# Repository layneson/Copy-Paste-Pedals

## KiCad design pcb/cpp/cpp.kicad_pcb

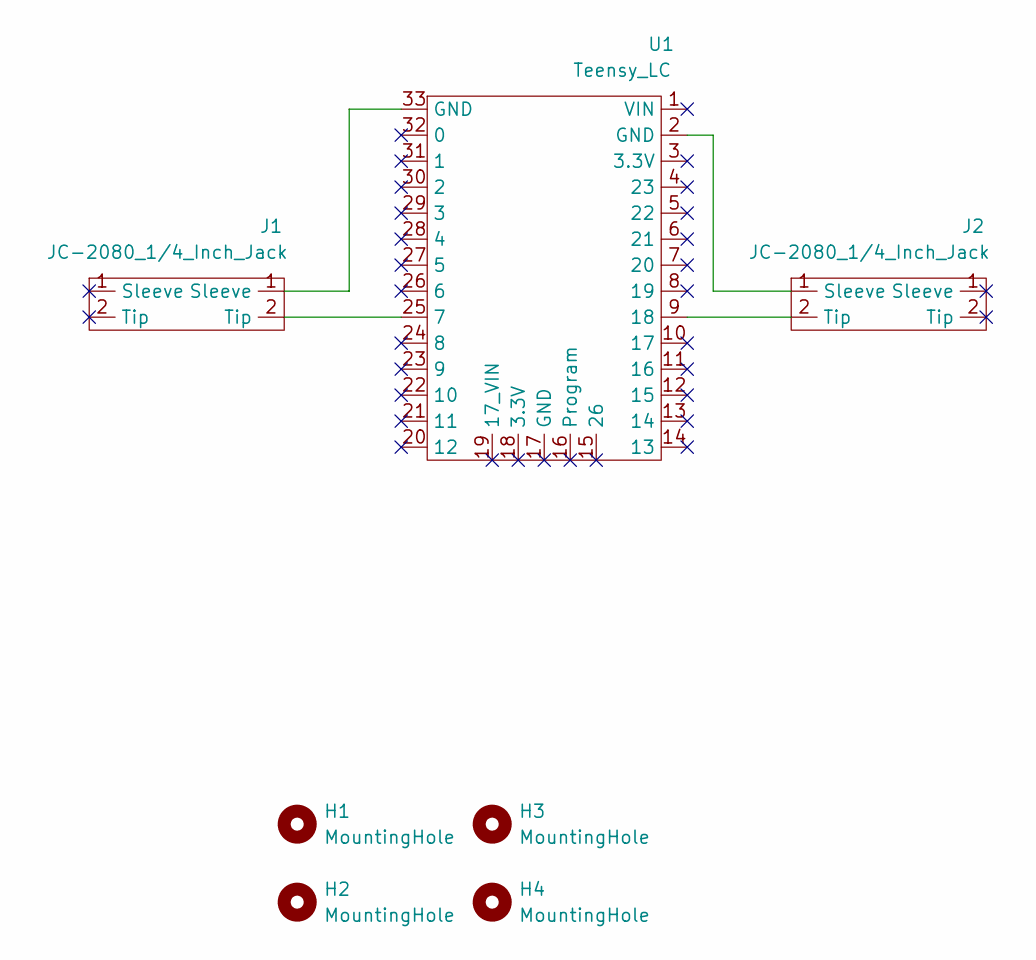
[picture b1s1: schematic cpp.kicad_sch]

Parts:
H1, H2, H3, H4: MountingHole; MountingHole_2.2mm_M2
J1, J2: JC-2080_1/4_Inch_Jack; JC-2080_14_Inch_Jack
U1: Teensy_LC; Teensy LC

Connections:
unnamed: J1.1 (Sleeve), U1.33 (GND)
unnamed: J1.2 (Tip), U1.25 (7)
unnamed: J2.1 (Sleeve), U1.2 (GND)
unnamed: J2.2 (Tip), U1.9 (18)

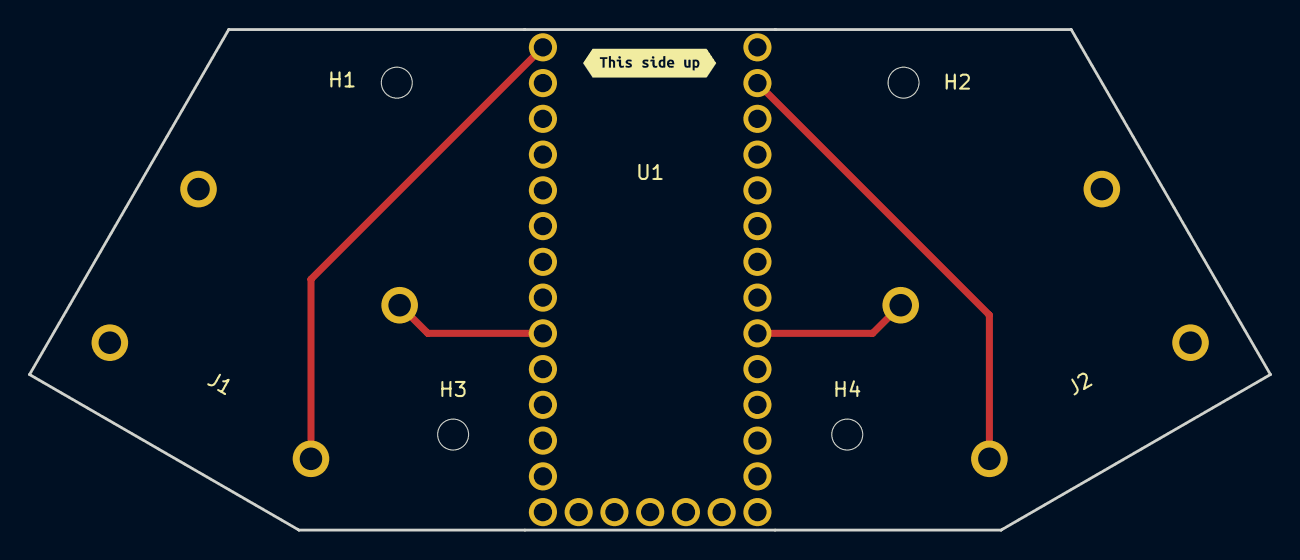
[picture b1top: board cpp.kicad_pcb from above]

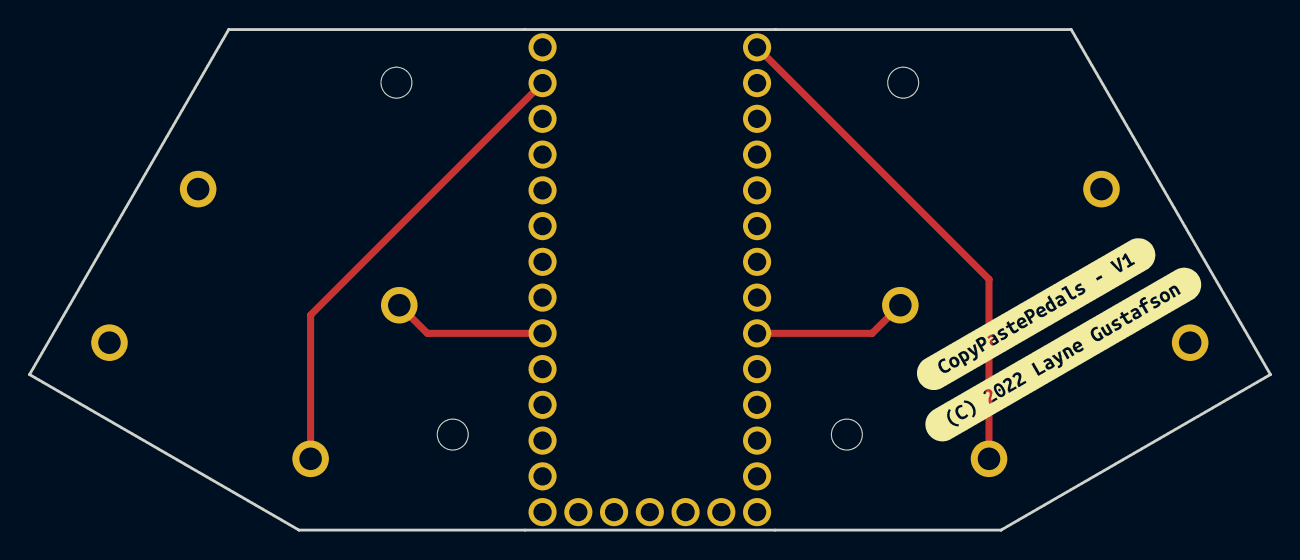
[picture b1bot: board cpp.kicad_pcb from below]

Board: 2 copper layers, 88.2 x 35.6 mm, 10 parts (2 on the bottom side), 4 nets.

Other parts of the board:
kibuzzard-622EB2CA: G***; kibuzzard-622EB2CA
kibuzzard-622EB217: G***; kibuzzard-622EB217
kibuzzard-622EB260: G***; kibuzzard-622EB260

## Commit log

2022-03-14 Code almost done, board almost done
2022-03-14 Set gerber export settings
2022-03-25 Set correct left and right pins
